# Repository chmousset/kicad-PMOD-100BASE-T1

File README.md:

# PMOD-LAN8720

This is a single-width PMOD module with the RMII DP83TC813 100BASE-T1 PHY.

## Master/Slave
**100BASE-T1 require one of the device to be setup as a Slave, and the other one as a Master.** This concept doesn't exist in 100BASE-T and most usual Ethernet types, and seems to be a particularity of 100BASE-T1 and 1000BASE-T1. Check R42 placement to setup Master/Slave mode.

## Configuration
Straps have been setup for RMII slave mode (refclk has to be supplied from the host at 50MHz), 100BASE-T1 Master Mode (R43 present) and MDIO PHYADD=0 (JP1 and JP2 open).

### Master/Slave
When R42 is placed, the DP83TC813 acts as a **Master**. When R42 isn't placed, the internal pulldown of the PHY enables the **Slave** mode.

### Phyaddress
MDIO PHY address is set with JP1 and JP2. 9 different addresses can be configured:

| JP1  | JP2  | PHYADD[0-1] | PHYADD[2-3] | PHYADD |
|------|------|-------------|-------------|--------|
| OPEN | OPEN | 0b00        | 0b00        | 0b0000 |
| 1-2  | OPEN | 0b11        | 0b00        | 0b0011 |
| 2-3  | OPEN | 0b01        | 0b00        | 0b0001 |
| OPEN | 1-2  | 0b00        | 0b11        | 0b1100 |
| 1-2  | 1-2  | 0b11        | 0b11        | 0b1111 |
| 2-3  | 1-2  | 0b01        | 0b11        | 0b1101 |
| OPEN | 2-3  | 0b00        | 0b01        | 0b0100 |
| 1-2  | 2-3  | 0b11        | 0b01        | 0b0111 |
| 2-3  | 2-3  | 0b01        | 0b01        | 0b0101 |

## Pinout
| Pin | type  | Function | Description          |
|-----|-------|----------|----------------------|
| 1   | I     | TX_D1    | Transmit Data        |
| 2   | I     | TXEN     | Transmit Enable      |
| 3   | O     | RX_D0    | Receive Data         |
| 4   | I     | REFCLK   | 50MHz clock          |
| 5   |       | GND      |                      |
| 6   |       | VCC      | 3.3V rail            |
| 7   | I     | TX_D0    | Transmit Data        |
| 8   | O     | RX_DV    | Receive / Data valid |
| 9   | O     | RX_D1    | Receive Data         |
| 10  | I, PU | RST_T1   | Reset                |
| 11  |       | GND      |                      |
| 12  |       | VCC      | 3.3V rail            |

Legend:
- I: input (ie. output from the host)
- O: output (ie. input from the host)
- PU: Pull-up

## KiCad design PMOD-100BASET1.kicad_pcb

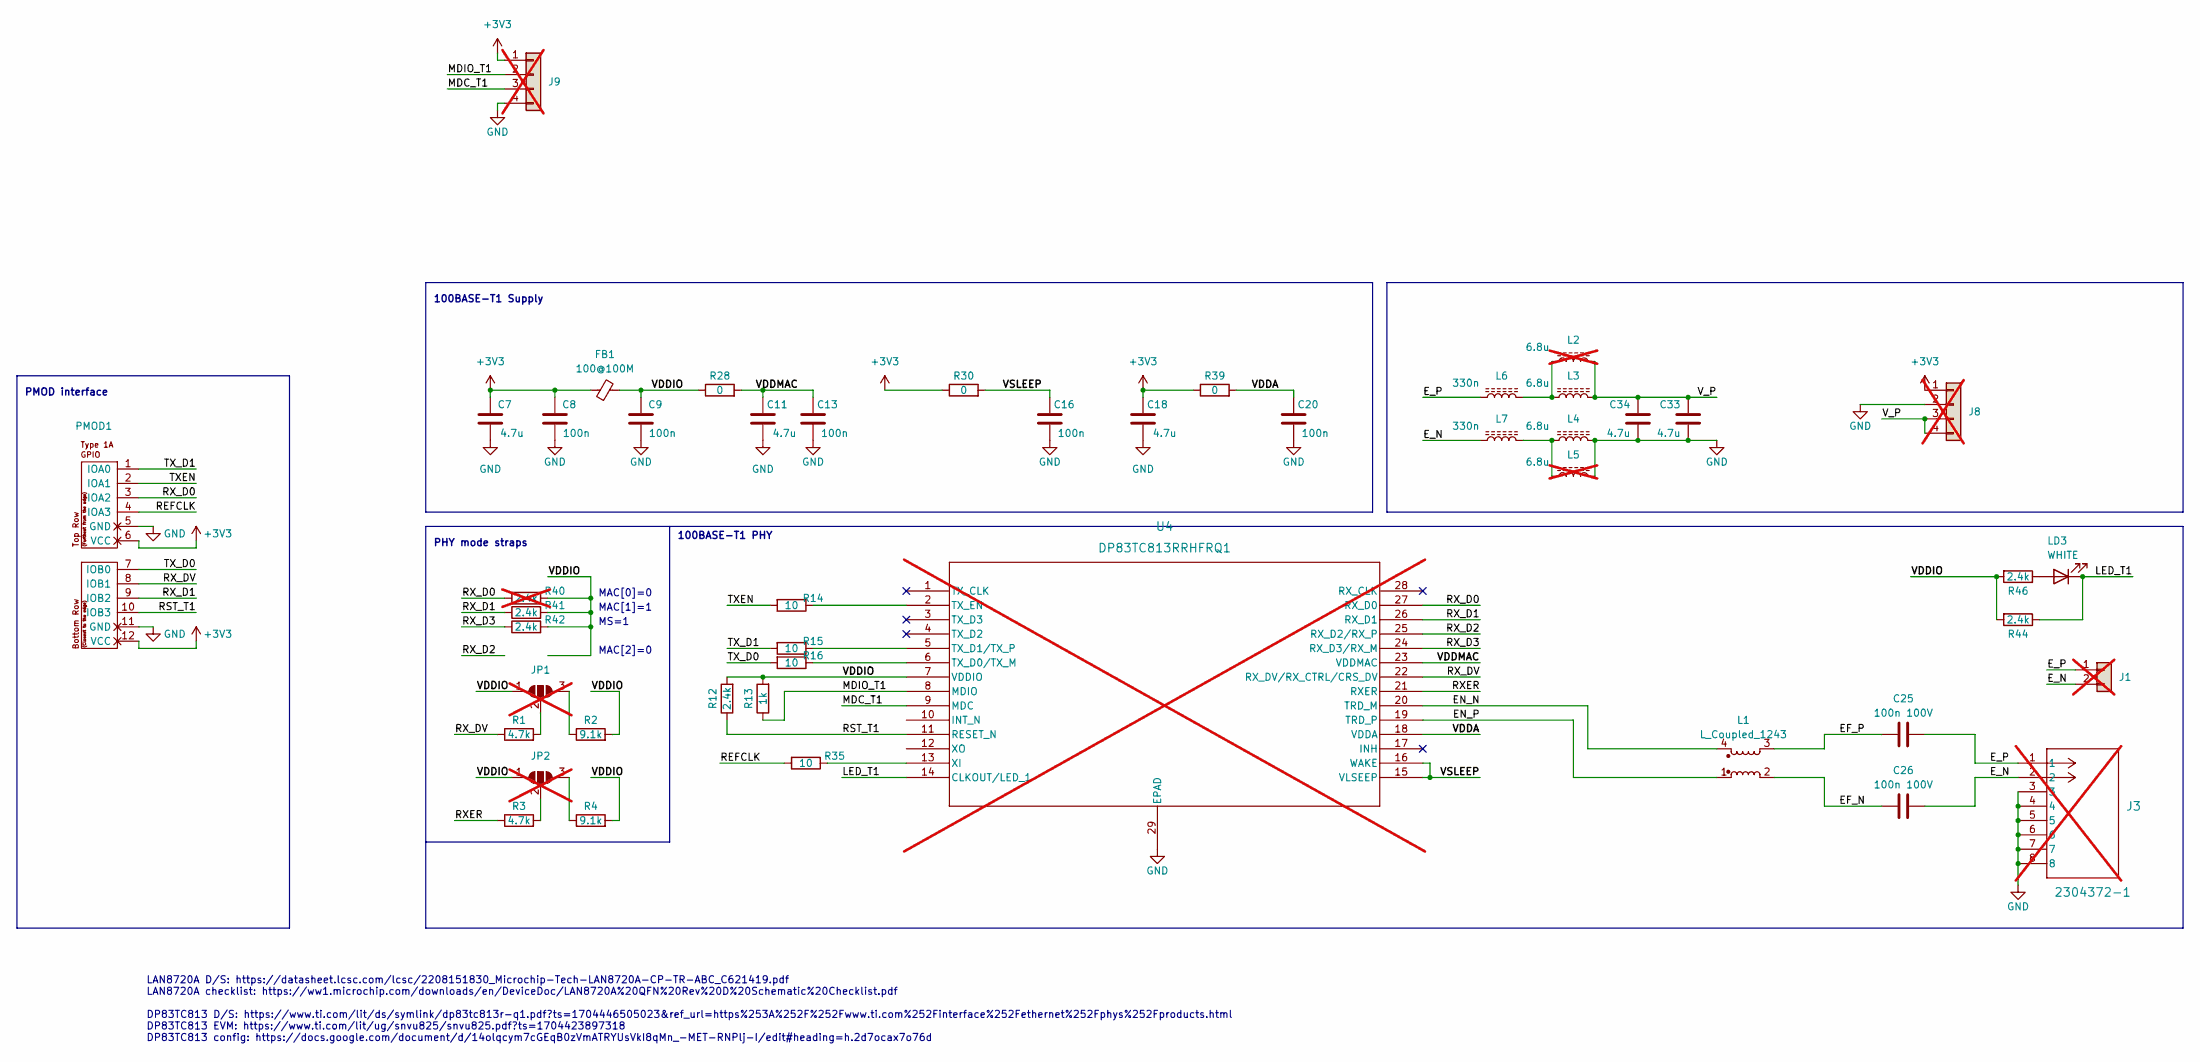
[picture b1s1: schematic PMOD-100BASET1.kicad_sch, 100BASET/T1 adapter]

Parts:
C7, C11, C18: 4.7u; C_0603_1608Metric; LCSC C19666
C8, C9, C13, C16, C20: 100n; C_0603_1608Metric; LCSC C14663
C25, C26: 100n 100V; C_0805_2012Metric; LCSC C28233
C33, C34: 4.7u; C_1206_3216Metric; LCSC C29823
FB1: 100@100M; R_0805_2012Metric; LCSC C1015
J1: Conn_01x02; B02B-JWPF-SK-R; LCSC C5305323; not fitted
J3: 2304372-1; CONN2_9-2304372_TEC; not fitted
J8, J9: Conn_01x03; PinHeader_1x04_P2.54mm_Vertical; not fitted
JP1, JP2: SolderJumper_3_Open; SolderJumper-3_P1.3mm_Open_RoundedPad1.0x1.5mm; not fitted
L1: L_Coupled_1243; FIL_DLW21SZ181XQ2L; LCSC C76896
L2, L5: 6.8u; L_6.3x6.3_H3; not fitted
L3, L4: 6.8u; L_1008_2520Metric; LCSC C2041474
L6, L7: 330n; R_0805_2012Metric; LCSC C92051
LD3: WHITE; LED_0603_1608Metric; LCSC C2290
PMOD1: PMOD-Device-x2-Type-1A-GPIO; pmod_pin_array_6x2; LCSC C492434
R1, R3: 4.7k; R_0603_1608Metric; LCSC C23162
R2, R4: 9.1k; R_0603_1608Metric; LCSC C23260
R12, R41, R42, R44, R46: 2.4k; R_0603_1608Metric; LCSC C22940
R13: 1k; R_0603_1608Metric; LCSC C21190
R14, R15, R16, R35: 10; R_0603_1608Metric; LCSC C22859
R28, R30, R39: 0; R_0603_1608Metric; LCSC C21189
R40: 2.4k; R_0603_1608Metric; LCSC C22940; not fitted
U4: DP83TC813RRHFRQ1; VQFN28_RHF_TEX; not fitted

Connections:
+3V3: C7.2, C8.2, C18.2, FB1.1, J8.1, J9.1, PMOD1.6 (VCC), PMOD1.12 (VCC), R30.1, R39.1
/EF_N: C26.2, L1.2
/EF_P: C25.2, L1.3
/EN_N: L1.4, U4.20 (TRD_M)
/EN_P: L1.1, U4.19 (TRD_P)
/E_N: C26.1, J1.2, J3.2, L7.2
/E_P: C25.1, J1.1, J3.1, L6.2
/LED_T1: LD3.1 (K), R44.1, U4.14 (CLKOUT/LED_1)
/MDC_T1: J9.3, U4.9 (MDC)
/MDIO_T1: J9.2, R13.1, U4.8 (MDIO)
/REFCLK: PMOD1.4 (IOA3), R35.2
/RST_T1: PMOD1.10 (IOB3), R12.1, U4.11 (RESET_N)
/RXER: R3.1, U4.21 (RXER)
/RX_D0: PMOD1.3 (IOA2), R40.1, U4.27 (RX_D0)
/RX_D1: PMOD1.9 (IOB2), R41.1, U4.26 (RX_D1)
/RX_D2: U4.25 (RX_D2/RX_P)
/RX_D3: R42.1, U4.24 (RX_D3/RX_M)
/RX_DV: PMOD1.8 (IOB1), R1.1, U4.22 (RX_DV/RX_CTRL/CRS_DV)
/TXEN: PMOD1.2 (IOA1), R14.2
/TX_D0: PMOD1.7 (IOB0), R16.2
/TX_D1: PMOD1.1 (IOA0), R15.2
/VDDA: C20.2, R39.2, U4.18 (VDDA)
/VDDIO: C9.2, FB1.2, JP1.1 (A), JP2.1 (A), R2.2, R4.2, R12.2, R13.2, R28.1, R40.2, R41.2, R42.2, R44.2, R46.2, U4.7 (VDDIO)
/VDDMAC: C11.2, C13.2, R28.2, U4.23 (VDDMAC)
/VSLEEP: C16.2, R30.2, U4.15 (VLSEEP), U4.16 (WAKE)
/V_P: C33.1, C34.1, J8.3, J8.4, L2.1, L3.1
GND: C7.1, C8.1, C9.1, C11.1, C13.1, C16.1, C18.1, C20.1, C33.2, C34.2, J3.3, J3.4, J3.5, J3.6, J3.7, J3.8, J8.2, J9.4, L4.1, L5.1, PMOD1.5 (GND), PMOD1.11 (GND), U4.29 (EPAD)
unnamed: JP1.3 (B), R2.1
unnamed: JP1.2 (C), R1.2
unnamed: JP2.3 (B), R4.1
unnamed: JP2.2 (C), R3.2
unnamed: L2.2, L3.2, L6.1
unnamed: L4.2, L5.2, L7.1
unnamed: LD3.2 (A), R46.1
unnamed: R16.1, U4.6 (TX_D0/TX_M)
unnamed: R15.1, U4.5 (TX_D1/TX_P)
unnamed: R14.1, U4.2 (TX_EN)
unnamed: R35.1, U4.13 (XI)

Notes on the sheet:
100BASE-T1 PHY
MAC[0]=0
100BASE-T1 Supply
PHY mode straps
MS=1
LAN8720A D/S: https://datasheet.lcsc.com/lcsc/2208151830_Microchip-Tech-LAN8720A-CP-TR-ABC_C621419.pdf LAN8720A checklist: https://ww1.microchip.com/downloads/en/DeviceDoc/LAN8720A%20QFN%20Rev%20D%20Schematic%20Checklist.pdf DP83TC813 D/S: https://www.ti.com/lit/ds/symlink/dp83tc813r-q1.pdf?ts=1704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
MAC[1]=1
PMOD interface
MAC[2]=0

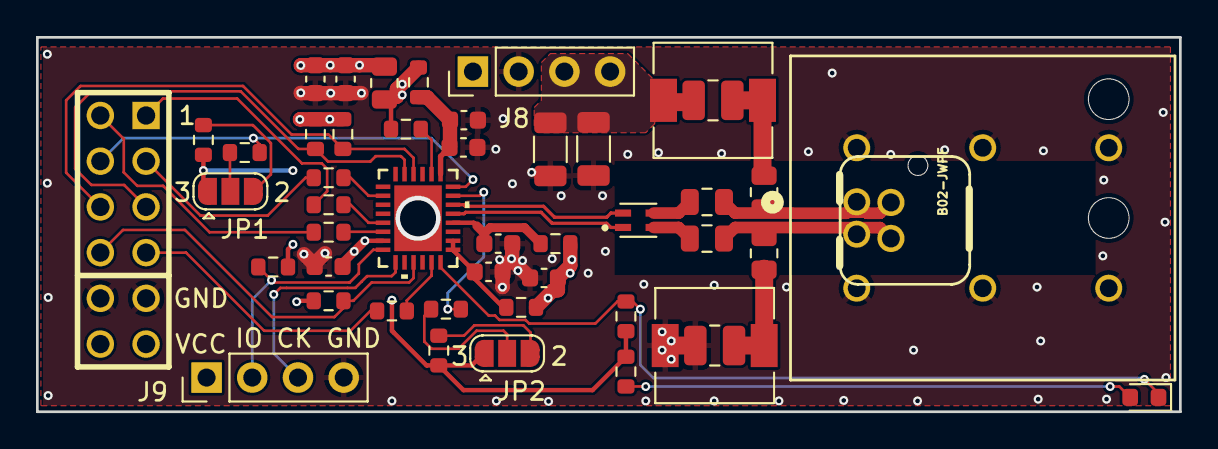
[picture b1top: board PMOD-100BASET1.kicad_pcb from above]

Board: 4 copper layers, 63.5 x 20.8 mm, 47 parts (0 on the bottom side), 37 nets.

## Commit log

2024-01-09 [init] first production
2024-04-17 [doc] added readme; updated files to Kicad V8
